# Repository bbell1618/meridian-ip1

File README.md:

# Meridian IP-1

A made-up surgical irrigation pump, designed down to a routed four-layer controller board, and a two-minute video in English and Mandarin that shows a board assembler one solder defect and exactly how to fix it.

**See it:** https://bbelllabs.com/work/meridian-ip1 (both videos, a 3D model you can turn and open, and the board record)

Everything here is a made-up example. "Meridian IP-1" is not a real product and no third-party design data was used. The package was produced with an AI-assisted pipeline that I directed.

## What is in this repository
- `video/meridian_ip1_j1_solder_fill_EN.mp4` — English narration, English + Chinese subtitles burnt in
- `video/meridian_ip1_j1_solder_fill_ZH.mp4` — Mandarin narration, same picture and subtitles
- `video/*.srt` — the subtitle text as separate files
- `cad/meridian_ip1.step` — full device assembly (enclosure, pump head, stepper + gearbox, pinch valve, sensors, fan, display, harnesses, board)
- `cad/meridian_ip1_mech.glb`, `cad/ip1_main_board.glb` — the same models for 3D viewers
- `cad/device.py` — the parametric CAD source (CadQuery)
- `pcb/ip1_main.kicad_pcb` — the routed 4-layer board (KiCad 7)
- `pcb/ip1_main.step` — board with component models
- `pcb/fab/` — Gerbers, drill file, placement file, parts list (BOM), netlist
- `pcb/board_def.py`, `pcb/make_board.py`, `pcb/patch_dsn.py` — the board source: parts, placement, netlist, build steps
- `pcb/ip1_main_drc.txt` — KiCad design-rule report

## The board
100 x 80 mm, 1.6 mm, 4 layers (signal + ground pour / ground plane / 3.3 V plane / signal + ground pour). 97 parts, 72 nets.
STM32F103 microcontroller; TMC2226 stepper driver (pump motor, J3); ADS1220 24-bit converter for two bridge pressure sensors (J5, J6);
optical bubble sensor input (J7); motor temperature input (J8); MOSFET switches with flyback diodes for the pinch valve (J4) and fan (J9);
24 V input with fuse, surge clamp and reverse-polarity diode (J1); 24 V to 5 V switching regulator; 3.3 V linear regulator;
RS-485 link to the display board (J11); EEPROM for calibration; debug header (J10).

Rev A detail the video is built on: J1 pin 2 (ground) joins the ground copper on layers 1, 2 and 4 with no thermal-relief spokes.

## Checked
- Netlist against footprints: every pad exists, no pad on two nets, deliberate no-connects listed.
- KiCad design-rule check on the finished board: 0 shorts, 0 clearance errors, 0 unconnected items.
  The 146 remaining items are 45 silkscreen label overlaps and 101 "footprint not linked to a library" notes; none are electrical.
- No overlapping parts; all parts inside the outline. Gerber, drill and placement files export.

## Not checked
- The board has not been built, powered or simulated.
- Component values come from data-sheet typical circuits and were not tuned.
- There is no drawn schematic; the circuit is the netlist table in `board_def.py`.
- Routing is from an autorouter (freerouting 1.9) plus scripted plane vias. No human review for noise, heat, creepage or medical safety spacing.
- The KiCad library has no 3D model for the 3.96 mm headers (J1, J3, J4); simple models of them are in the device assembly, not in `ip1_main.step`.
- Mechanical parts are simplified shapes at true size.

## Facts used in the video (with where they come from)
- Minimum 75% vertical solder fill of a plated through-hole for Class 3: IPC J-STD-001 / IPC-A-610.
- Cause on plane-connected pins: heat sinking into the copper planes. Fixes: more top-side preheat (hole copper at 110 C or more before the wave),
  longer contact time, flux through the full hole, and thermal-relief pads in the design.
- Fill must be verified by X-ray or cross-section because the connector body hides the top side.
- The "about 40% fill" figure is an illustration for this made-up case, not a measurement.

## Narration
Computer-generated voices (Piper: en_US "ryan", zh_CN "huayan"). The Chinese wording and factory terms (透锡, 波峰焊, 链速, 花焊盘) should get a native-speaker check before this is used with a real supplier.

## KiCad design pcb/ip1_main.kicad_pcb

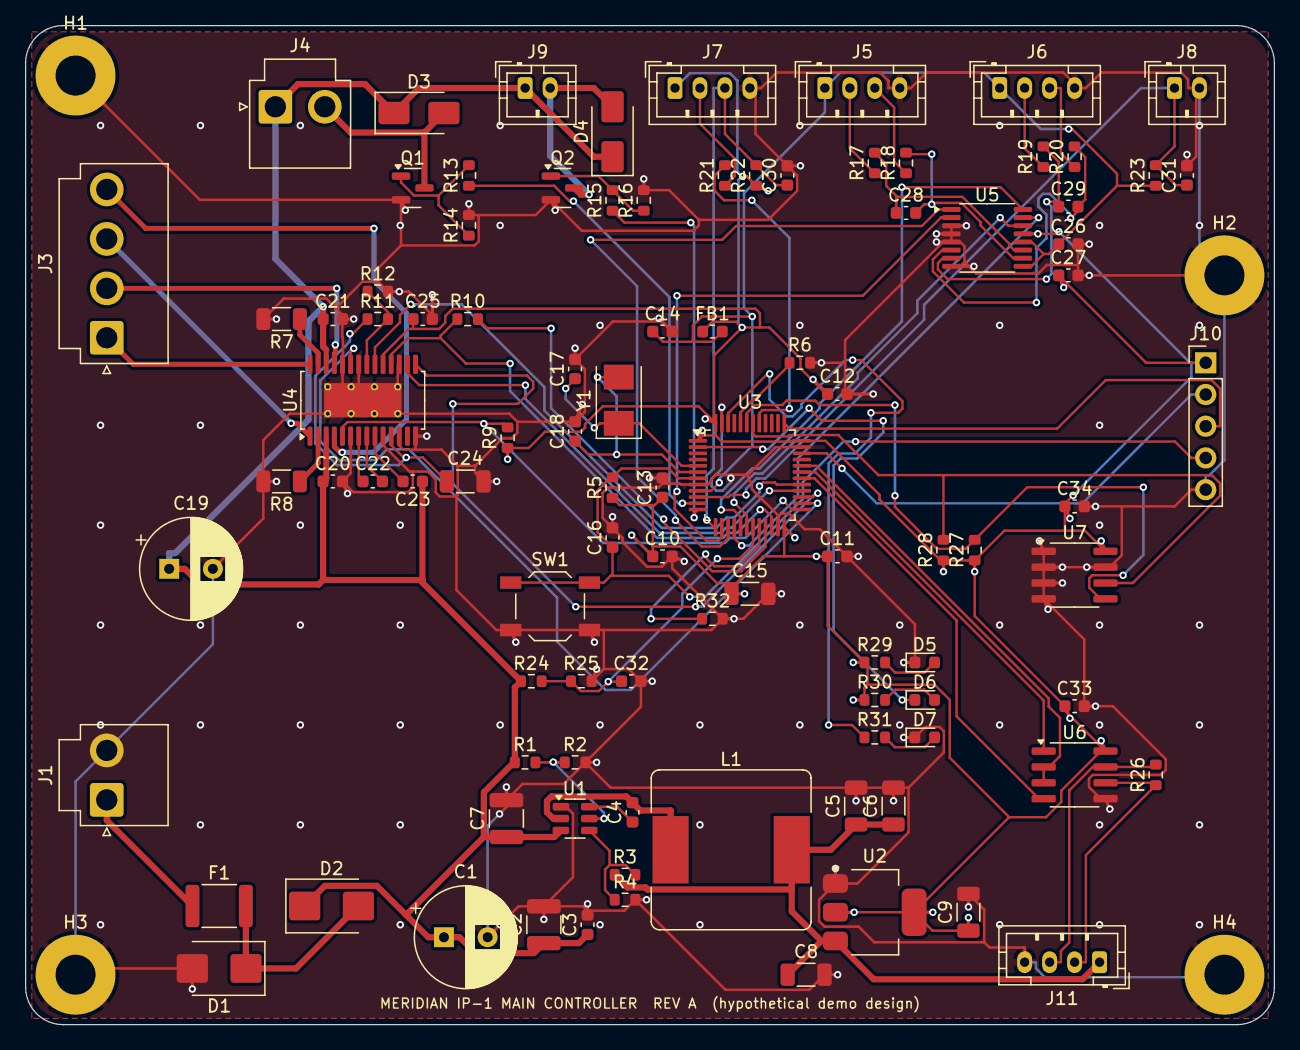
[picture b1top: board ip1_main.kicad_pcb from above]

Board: 4 copper layers, 100.0 x 80.0 mm, 101 parts (0 on the bottom side), 72 nets.

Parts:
C1: 220u 35V; CP_Radial_D8.0mm_P3.50mm
C2, C7: 10u 50V; C_1210_3225Metric
C3, C4, C10, C11, C12, C13, C16, C20, C21, C23, C25, C26, C27, C28, C29, C31, C32, C33, C34: 100n; C_0603_1608Metric
C5, C6, C9: 22u; C_1206_3216Metric
C8: 10u; C_1206_3216Metric
C14: 1u; C_0603_1608Metric
C15: 4u7; C_1206_3216Metric
C17, C18: 18p; C_0603_1608Metric
C19: 100u 35V; CP_Radial_D8.0mm_P3.50mm
C22: 22n; C_0603_1608Metric
C24: 2u2; C_1206_3216Metric
C30: 10n; C_0603_1608Metric
D1: SMBJ28A; D_SMB
D2: B340; D_SMB
D3, D4: SS34; D_SMA
D5: GRN PWR; LED_0603_1608Metric
D6: GRN RUN; LED_0603_1608Metric
D7: RED FAULT; LED_0603_1608Metric
F1: PTC 3A; Fuse_1812_4532Metric
FB1: 600R; L_0603_1608Metric
H1, H2, H3, H4: M3; MountingHole_3.2mm_M3_Pad
J1: 24V IN; JST_VH_B2P-VH_1x02_P3.96mm_Vertical
J3: PUMP MOTOR; JST_VH_B4P-VH_1x04_P3.96mm_Vertical
J4: PINCH VALVE; JST_VH_B2P-VH_1x02_P3.96mm_Vertical
J5: PRESSURE IN; JST_PH_B4B-PH-K_1x04_P2.00mm_Vertical
J6: PRESSURE OUT; JST_PH_B4B-PH-K_1x04_P2.00mm_Vertical
J7: BUBBLE; JST_PH_B4B-PH-K_1x04_P2.00mm_Vertical
J8: MOTOR NTC; JST_PH_B2B-PH-K_1x02_P2.00mm_Vertical
J9: FAN; JST_PH_B2B-PH-K_1x02_P2.00mm_Vertical
J10: SWD; PinHeader_1x05_P2.54mm_Vertical
J11: UI RS485; JST_PH_B4B-PH-K_1x04_P2.00mm_Vertical
L1: 10u 5A; L_Bourns_SRR1260
Q1, Q2: AO3400A; SOT-23
R1, R3, R14, R16, R24: 100k; R_0603_1608Metric
R2: 22k; R_0603_1608Metric
R4: 13.3k; R_0603_1608Metric
R5, R6, R9, R11, R22, R23, R25, R32: 10k; R_0603_1608Metric
R7, R8: 0R11; R_1206_3216Metric
R10, R17, R18, R19, R20, R29, R30, R31: 1k; R_0603_1608Metric
R12: 20k; R_0603_1608Metric
R13, R15: 100R; R_0603_1608Metric
R21: 150R; R_0603_1608Metric
R26: 120R; R_0603_1608Metric
R27, R28: 4k7; R_0603_1608Metric
SW1: RESET; SW_SPST_TL3342
U1: TPS54202; SOT-23-6
U2: AMS1117-3.3; SOT-223-3_TabPin2
U3: STM32F103C8T6; LQFP-48_7x7mm_P0.5mm
U4: TMC2226; HTSSOP-28-1EP_4.4x9.7mm_P0.65mm_EP2.75x6.2mm_ThermalVias
U5: ADS1220; TSSOP-16_4.4x5mm_P0.65mm
U6: MAX3485; SOIC-8_3.9x4.9mm_P1.27mm
U7: 24LC256; SOIC-8_3.9x4.9mm_P1.27mm
Y1: 8MHz; Crystal_SMD_5032-2Pin_5.0x3.2mm

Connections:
+3V3: C9.1, C10.1, C11.1, C12.1, C13.1, C15.1, C25.1, C27.1, C33.1, C34.1, FB1.1, J7.1, J10.1, R5.1, R9.1, R22.1, R27.1, R28.1, R29.1, R30.1, U2.2, U3.1, U3.24, U3.36, U3.48, U4.19, U5.13, U6.8, U7.8
+3V3A: C14.1, C26.1, FB1.2, J5.1, J6.1, R23.1, U3.9, U5.9, U5.12
+5V: C5.1, C6.1, C8.1, J11.1, L1.2, R3.1, U2.3
+24V: C1.1, C2.1, C3.1, C7.1, C19.1, C20.1, C21.1, C23.1, D2.1, D3.1, D4.1, J4.1, J9.1, R1.1, R24.1, U1.3, U4.3, U4.26
+24V_IN: F1.1, J1.1
ADC_CS_N: U3.14, U5.2
ADC_DRDY_N: U3.18, U5.14
ADC_MISO: U3.16, U5.15
ADC_MOSI: U3.17, U5.16
ADC_SCK: U3.15, U5.1
BOOT0: R6.1, U3.44
BOOT1: R32.1, U3.20
BUB_LED_DRV: R21.2, U3.41
BUB_LED_K: J7.2, R21.1
BUB_SIG: C30.1, J7.3, R22.2, U3.13
BUCK_BOOT: C4.1, U1.6
BUCK_EN: R1.2, R2.1, U1.5
BUCK_FB: R3.2, R4.1, U1.4
BUCK_SW: C4.2, L1.1, U1.2
CP_I: C22.2, U4.8
CP_O: C22.1, U4.7
DRV_5V: C24.1, R11.1, U4.11
DRV_DIAG: U3.27, U4.15
DRV_DIR: U3.26, U4.23
DRV_EN_N: R9.2, U3.25, U4.5
DRV_INDEX: U3.28, U4.16
DRV_STEP: U3.29, U4.20
DRV_UART: R10.1, U3.22, U4.18
DRV_UART_TX: R10.2, U3.21
DRV_VREF: R11.2, R12.1, U4.21
FAN_CTL: R15.1, U3.12
FAN_G: Q2.1, R15.2, R16.1
FAN_N: D4.2, J9.2, Q2.3
GND: C1.2, C2.2, C3.2, C5.2, C6.2, C7.2, C8.2, C9.2, C10.2, C11.2, C12.2, C13.2, C14.2, C15.2, C16.2, C17.2, C18.2, C19.2, C20.2, C21.2, C24.2, C25.2, C26.2, C27.2, C30.2, C31.2, C32.2, C33.2, C34.2, D1.2, D5.1, D7.1, H1.1, H2.1, H3.1, H4.1, J1.2, J5.4, J6.4, J7.4, J8.2, J10.5, J11.4, Q1.2, Q2.2, R2.2, R4.2, R6.2, R7.2, R8.2, R12.2, R14.2, R16.2, R25.2, R32.2, SW1.2, U1.1, U2.1, U3.8, U3.23, U3.35, U3.47, U4.6, U4.10, U4.12, U4.14, U4.17, U4.22, U4.24, U4.29, U5.3, U5.4, U5.5, U5.8, U6.5, U7.1, U7.2, U7.3, U7.4, U7.7
I2C_SCL: R28.2, U3.42, U7.6
I2C_SDA: R27.2, U3.43, U7.5
LED_FLT: R31.1, U3.46
LED_FLT_A: D7.2, R31.2
LED_PWR: D5.2, R29.2
LED_RUN: D6.1, U3.2
LED_RUN_A: D6.2, R30.2
MOT_A1: J3.1, U4.28
MOT_A2: J3.2, U4.25
MOT_B1: J3.3, U4.1
MOT_B2: J3.4, U4.4
NRST: C16.1, J10.4, R5.2, SW1.1, U3.7
NTC: C31.1, J8.1, R23.2, U3.10
OSC_IN: C17.1, U3.5, Y1.1
OSC_OUT: C18.1, U3.6, Y1.2
P1N: C28.2, R18.2, U5.10
P1N_IN: J5.3, R18.1
P1P: C28.1, R17.2, U5.11
P1P_IN: J5.2, R17.1
P2N: C29.2, R20.2, U5.6
P2N_IN: J6.3, R20.1
P2P: C29.1, R19.2, U5.7
P2P_IN: J6.2, R19.1
RS485_A: J11.2, R26.1, U6.6
RS485_B: J11.3, R26.2, U6.7
RS485_DE: U3.32, U6.2, U6.3
RS485_DI: U3.30, U6.4
RS485_RO: U3.31, U6.1
SENSE_A: R7.1, U4.27
SENSE_B: R8.1, U4.2
SWCLK: J10.3, U3.37
SWDIO: J10.2, U3.34
VALVE_CTL: R13.1, U3.11
VALVE_G: Q1.1, R13.2, R14.1
VALVE_N: D3.2, J4.2, Q1.3
VCP: C23.2, U4.9
VFUSE: D1.1, D2.2, F1.2
VMON: C32.1, R24.2, R25.1, U3.19

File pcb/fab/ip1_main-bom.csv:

Qty,References,Value,Footprint
1,J1,24V IN,Connector_JST:JST_VH_B2P-VH_1x02_P3.96mm_Vertical
1,F1,PTC 3A,Fuse:Fuse_1812_4532Metric
1,D1,SMBJ28A,Diode_SMD:D_SMB
1,D2,B340,Diode_SMD:D_SMB
1,C1,220u 35V,Capacitor_THT:CP_Radial_D8.0mm_P3.50mm
2,C2 C7,10u 50V,Capacitor_SMD:C_1210_3225Metric
19,C3 C4 C20 C21 C23 C25 C10 C11 C12 C13 C16 C28 C29 C26 C27 C31 C32 C33 C34,100n,Capacitor_SMD:C_0603_1608Metric
1,U1,TPS54202,Package_TO_SOT_SMD:SOT-23-6
5,R1 R3 R14 R16 R24,100k,Resistor_SMD:R_0603_1608Metric
1,R2,22k,Resistor_SMD:R_0603_1608Metric
1,L1,10u 5A,Inductor_SMD:L_Bourns_SRR1260
1,R4,13.3k,Resistor_SMD:R_0603_1608Metric
3,C5 C6 C9,22u,Capacitor_SMD:C_1206_3216Metric
1,U2,AMS1117-3.3,Package_TO_SOT_SMD:SOT-223-3_TabPin2
1,C8,10u,Capacitor_SMD:C_1206_3216Metric
1,U4,TMC2226,Package_SO:HTSSOP-28-1EP_4.4x9.7mm_P0.65mm_EP2.75x6.2mm_ThermalVias
1,J3,PUMP MOTOR,Connector_JST:JST_VH_B4P-VH_1x04_P3.96mm_Vertical
1,C19,100u 35V,Capacitor_THT:CP_Radial_D8.0mm_P3.50mm
2,R7 R8,0R11,Resistor_SMD:R_1206_3216Metric
1,C22,22n,Capacitor_SMD:C_0603_1608Metric
1,C24,2u2,Capacitor_SMD:C_1206_3216Metric
8,R9 R11 R5 R6 R32 R22 R23 R25,10k,Resistor_SMD:R_0603_1608Metric
8,R10 R17 R18 R19 R20 R29 R30 R31,1k,Resistor_SMD:R_0603_1608Metric
1,R12,20k,Resistor_SMD:R_0603_1608Metric
1,J4,PINCH VALVE,Connector_JST:JST_VH_B2P-VH_1x02_P3.96mm_Vertical
2,Q1 Q2,AO3400A,Package_TO_SOT_SMD:SOT-23
2,D3 D4,SS34,Diode_SMD:D_SMA
2,R13 R15,100R,Resistor_SMD:R_0603_1608Metric
1,J9,FAN,Connector_JST:JST_PH_B2B-PH-K_1x02_P2.00mm_Vertical
1,U3,STM32F103C8T6,Package_QFP:LQFP-48_7x7mm_P0.5mm
1,Y1,8MHz,Crystal:Crystal_SMD_5032-2Pin_5.0x3.2mm
2,C17 C18,18p,Capacitor_SMD:C_0603_1608Metric
1,C14,1u,Capacitor_SMD:C_0603_1608Metric
1,C15,4u7,Capacitor_SMD:C_1206_3216Metric
1,FB1,600R,Inductor_SMD:L_0603_1608Metric
1,SW1,RESET,Button_Switch_SMD:SW_SPST_TL3342
1,J10,SWD,Connector_PinHeader_2.54mm:PinHeader_1x05_P2.54mm_Vertical
1,U5,ADS1220,Package_SO:TSSOP-16_4.4x5mm_P0.65mm
1,J5,PRESSURE IN,Connector_JST:JST_PH_B4B-PH-K_1x04_P2.00mm_Vertical
1,J6,PRESSURE OUT,Connector_JST:JST_PH_B4B-PH-K_1x04_P2.00mm_Vertical
1,J7,BUBBLE,Connector_JST:JST_PH_B4B-PH-K_1x04_P2.00mm_Vertical
1,R21,150R,Resistor_SMD:R_0603_1608Metric
1,C30,10n,Capacitor_SMD:C_0603_1608Metric
1,J8,MOTOR NTC,Connector_JST:JST_PH_B2B-PH-K_1x02_P2.00mm_Vertical
1,U6,MAX3485,Package_SO:SOIC-8_3.9x4.9mm_P1.27mm
1,R26,120R,Resistor_SMD:R_0603_1608Metric
1,J11,UI RS485,Connector_JST:JST_PH_B4B-PH-K_1x04_P2.00mm_Vertical
1,U7,24LC256,Package_SO:SOIC-8_3.9x4.9mm_P1.27mm
2,R27 R28,4k7,Resistor_SMD:R_0603_1608Metric
1,D5,GRN PWR,LED_SMD:LED_0603_1608Metric
1,D6,GRN RUN,LED_SMD:LED_0603_1608Metric
1,D7,RED FAULT,LED_SMD:LED_0603_1608Metric
